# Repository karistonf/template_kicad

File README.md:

# Template Kicad

Some templates that are very useful for developing PCBs in KiCad

The components in the template include:

* A symmetrical power supply with an input of 5 volts and outputs of +12 volts and -12 volts.
* Can (Controller Area Network) module
* A buck power supply with an input of 12 volts and an output of 3.3 volts.
* A microcontroller, the STM32F103, featuring a High-speed external (HSE) crystal, a Low-speed external (LSE) crystal for the RTC, a 3.3V battery backup for the RTC, power indicator LEDs, a USB connector, and a programming connector with a JST jack.

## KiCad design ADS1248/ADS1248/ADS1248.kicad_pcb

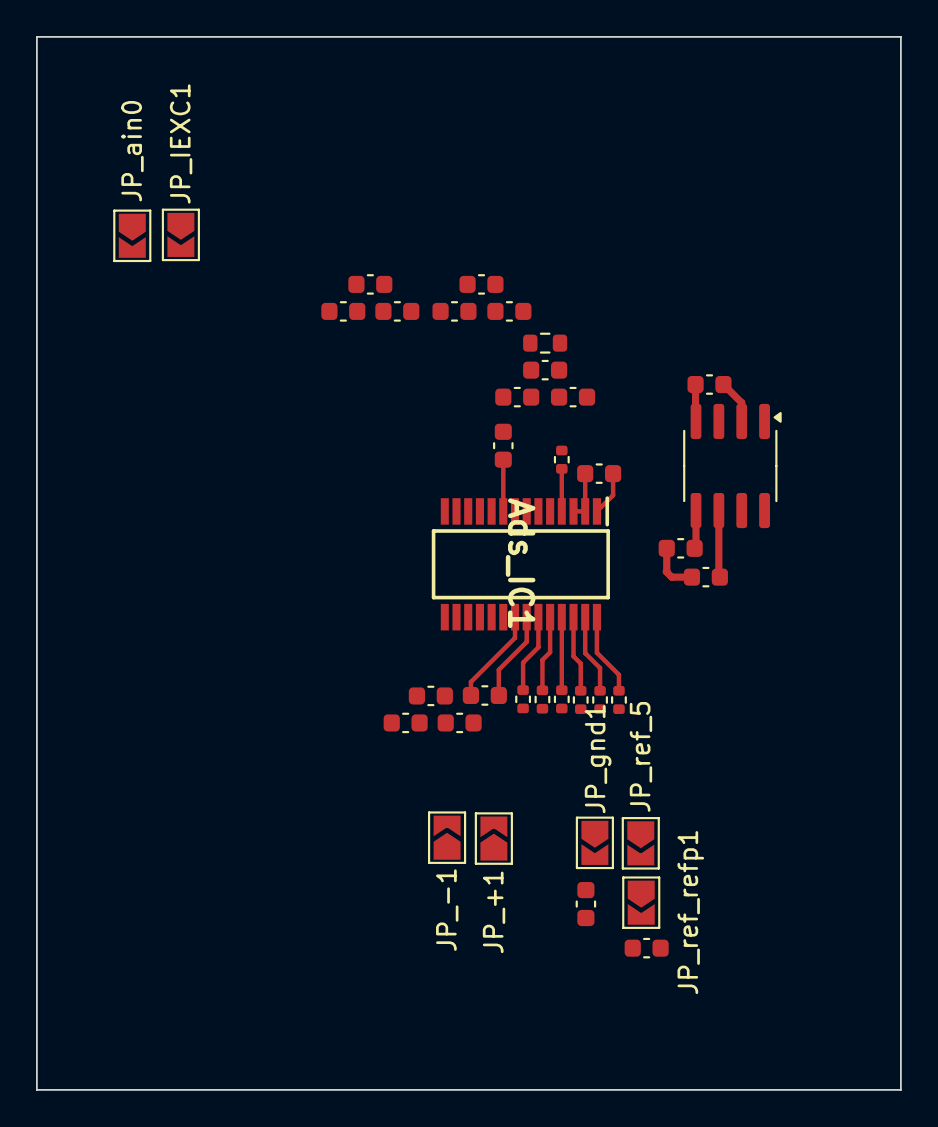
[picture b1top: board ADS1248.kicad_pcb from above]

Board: 2 copper layers, 48.0 x 58.5 mm, 37 parts (0 on the bottom side), 22 nets.

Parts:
Ads_C1, Ads_C2, Ads_C3: 0.1uF; C_0603_1608Metric
Ads_IC1: ADS1248IPWR; SOP65P640X120-28N
Ads_R1, Ads_R2, Ads_R3, Ads_R4, Ads_R5, Ads_R6, Ads_R7: 47; R_0402_1005Metric
Ads_ain_C1, Ads_ain_C2, Ads_ain_C3, Ads_ain_C4, Ads_ain_C5, Ads_ain_C6: 0.1uF; C_0603_1608Metric
Ads_ref_0_C1, Ads_ref_0_C2, Ads_ref_0_C3, Ads_ref_1_C1, Ads_ref_1_C2: 0.1uF; C_0603_1608Metric
CRTD_I_CM5, CRTD_I_CM6: C; C_0603_1608Metric
CRTD_I_DIFF3: C; C_0603_1608Metric
JP_+1: Jumper_2_Open; SolderJumper-2_P1.3mm_Open_TrianglePad1.0x1.5mm
JP_-1: Jumper_2_Open; SolderJumper-2_P1.3mm_Open_TrianglePad1.0x1.5mm
JP_IEXC1: Jumper_2_Open; SolderJumper-2_P1.3mm_Open_TrianglePad1.0x1.5mm
JP_ain0: Jumper_2_Open; SolderJumper-2_P1.3mm_Open_TrianglePad1.0x1.5mm
JP_gnd1: Jumper_2_Open; SolderJumper-2_P1.3mm_Open_TrianglePad1.0x1.5mm
JP_ref_5: Jumper_2_Open; SolderJumper-2_P1.3mm_Open_TrianglePad1.0x1.5mm
JP_ref_refp1: Jumper_2_Open; SolderJumper-2_P1.3mm_Open_TrianglePad1.0x1.5mm
REF1: 10K; R_0603_1608Metric
Ref_C1, Ref_C3: 1uF; C_0603_1608Metric
Ref_C2: 22uF; C_0603_1608Metric
U1: REF5050AD; SOIC-8_3.9x4.9mm_P1.27mm

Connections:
+3.3V: Ads_C1.1, Ads_IC1.1 (DVDD)
/5V: Ref_C1.2, U1.2 (Vin)
AVDD: Ads_C3.1, Ads_IC1.22 (AVDD), JP_ref_5.2 (B), JP_ref_refp1.1 (A), Ref_C2.1, U1.6 (Vout)
AVSS: Ads_C1.2, Ads_C2.2, Ads_C3.2, Ads_IC1.2 (DGND), Ads_IC1.3 (CLK), Ads_IC1.8 (REFN1), Ads_IC1.10 (VREFCOM), Ads_IC1.21 (AVSS), Ads_ain_C1.1, Ads_ain_C3.2, Ads_ain_C4.1, Ads_ain_C6.2, Ads_ref_0_C1.1, Ads_ref_0_C3.2, Ads_ref_1_C1.1, Ads_ref_1_C2.2, CRTD_I_CM5.1, CRTD_I_CM6.2, JP_gnd1.2 (B), Ref_C1.1, Ref_C2.2, Ref_C3.2, U1.4 (GND)
IEXC1: Ads_IC1.20 (IEXC1), JP_IEXC1.1 (A)
unnamed: Ads_IC1.27 (DIN), Ads_R3.1
unnamed: Ads_IC1.26 (DOUT/~DRDY), Ads_R4.1
unnamed: Ads_IC1.28 (SCLK), Ads_R2.1
unnamed: Ads_IC1.23 (START), Ads_R7.1
unnamed: Ads_IC1.24 (~CS), Ads_R6.1
unnamed: Ads_IC1.25 (~DRDY), Ads_R5.1
unnamed: Ads_IC1.4 (~RESET), Ads_R1.2
unnamed: Ref_C3.1, U1.5 (Trim/NR)
REFN0: Ads_IC1.6 (REFN0/GPIO1), Ads_ref_0_C2.2, Ads_ref_0_C3.1, REF1.1
REFP0: Ads_IC1.5 (REFP0/GPIO0), Ads_IC1.14 (AIN5/IEXC/GPIO5), Ads_IC1.17 (AIN2/IEXC/GPIO2), Ads_ain_C2.2, Ads_ain_C3.1, Ads_ain_C5.2, Ads_ain_C6.1, Ads_ref_0_C1.2, Ads_ref_0_C2.1, REF1.2
REFP1: Ads_IC1.7 (REFP1), Ads_ref_1_C1.2, Ads_ref_1_C2.1, JP_ref_refp1.2 (B)
VRefOut: Ads_C2.1, Ads_IC1.9 (VREFOUT)
ain0: Ads_IC1.11 (AIN0/IEXC), JP_ain0.1 (A)
ain1: Ads_IC1.12 (AIN1/IEXC), Ads_ain_C4.2, Ads_ain_C5.1, JP_IEXC1.2 (B), JP_ain0.2 (B)
ain3: Ads_IC1.13 (AIN4/IEXC/GPIO4), Ads_IC1.18 (AIN3/IEXC/GPIO3), Ads_ain_C1.2, Ads_ain_C2.1
ain6: Ads_IC1.15 (AIN6/IEXC/GPIO6), CRTD_I_CM5.2, CRTD_I_DIFF3.1, JP_+1.2 (B)
ain7: Ads_IC1.16 (AIN7/IEXC/GPIO7), CRTD_I_CM6.1, CRTD_I_DIFF3.2, JP_-1.2 (B)

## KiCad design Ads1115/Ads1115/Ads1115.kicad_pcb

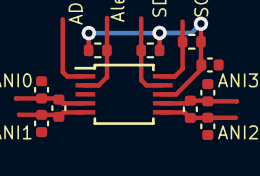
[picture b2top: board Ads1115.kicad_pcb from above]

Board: 2 copper layers, 11 parts (0 on the bottom side), 9 nets.

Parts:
ADC_Alert_R1: 10k; R_0402_1005Metric
ADC_C1, ADC_C2, ADC_C3, ADC_C4, ADC_C5, ADC_C6, ADC_C7: 0.1uF; C_0402_1005Metric
ADC_SCL_R1: 10k; R_0402_1005Metric
ADC_SDA_R1: 10k; R_0402_1005Metric
ADS1115_U1: ADS1115IDGS; TSSOP-10_3x3mm_P0.5mm

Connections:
+5V: ADC_Alert_R1.1, ADC_C1.2, ADC_SCL_R1.1, ADC_SDA_R1.2, ADS1115_U1.8 (VDD)
/Alert: ADC_Alert_R1.2, ADS1115_U1.2 (ALERT/RDY)
/SCL: ADC_SCL_R1.2, ADS1115_U1.10 (SCL)
/SDA: ADC_SDA_R1.1, ADS1115_U1.9 (SDA)
A0: ADC_C2.2, ADC_C6.2, ADS1115_U1.4 (AIN0)
A1: ADC_C3.2, ADC_C6.1, ADS1115_U1.5 (AIN1)
A2: ADC_C4.2, ADC_C7.1, ADS1115_U1.6 (AIN2)
A3: ADC_C5.2, ADC_C7.2, ADS1115_U1.7 (AIN3)
GND: ADC_C1.1, ADC_C2.1, ADC_C3.1, ADC_C4.1, ADC_C5.1, ADS1115_U1.1 (ADDR), ADS1115_U1.3 (GND)

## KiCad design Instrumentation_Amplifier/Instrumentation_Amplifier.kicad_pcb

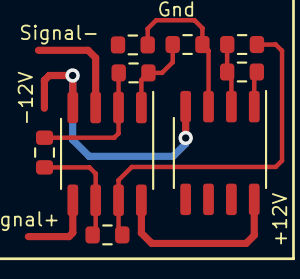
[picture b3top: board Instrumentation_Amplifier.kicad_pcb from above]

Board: 2 copper layers, 9 parts (0 on the bottom side), 9 nets.

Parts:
IA_R1: 1k; R_0603_1608Metric
IA_R2, IA_R3: 470; R_0603_1608Metric
IA_R4, IA_R5: 10k; R_0603_1608Metric
IA_R6, IA_R7: 100k; R_0603_1608Metric
IA_U1, IA_U2: LM358; SO-8_3.9x4.9mm_P1.27mm

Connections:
+12L: IA_U1.8 (V+), IA_U2.8 (V+)
-12V: IA_U1.4 (V-), IA_U2.4 (V-)
/Signal_Out: IA_R7.1, IA_U2.1
unnamed: IA_R2.2, IA_R5.1, IA_U1.1
unnamed: IA_R3.2, IA_R4.1, IA_U1.7
unnamed: IA_R1.2, IA_R2.1, IA_U1.2 (-)
unnamed: IA_R1.1, IA_R3.1, IA_U1.6 (-)
unnamed: IA_R5.2, IA_R6.2, IA_U2.3 (+)
unnamed: IA_R4.2, IA_R7.2, IA_U2.2 (-)

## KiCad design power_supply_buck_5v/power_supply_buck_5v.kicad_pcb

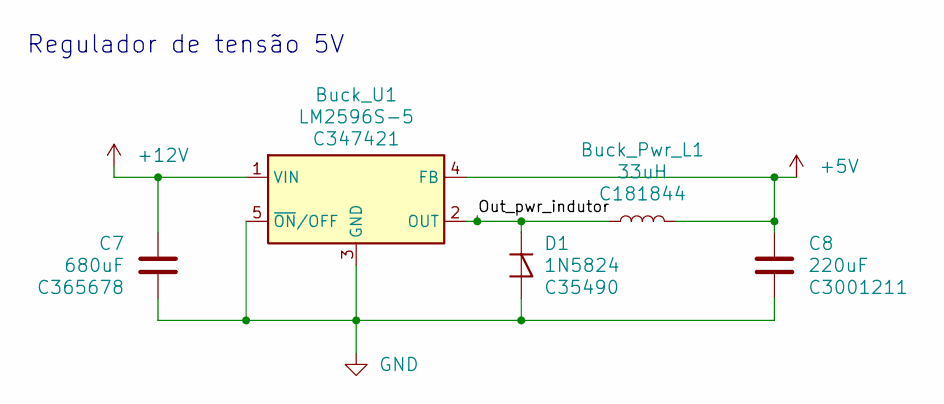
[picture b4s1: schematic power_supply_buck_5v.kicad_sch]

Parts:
Buck_Pwr_L1: 33uH; L_12x12mm_H8mm; LCSC C181844
Buck_U1: LM2596S-5; TO-263-5_TabPin3; LCSC C347421
C7: 680uF; CP_Elec_10x10.5; LCSC C365678
C8: 220uF; CP_Elec_6.3x5.4; LCSC C3001211
D1: 1N5824; D_SMB; LCSC C35490

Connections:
+5V: Buck_Pwr_L1.2, Buck_U1.4 (FB), C8.1
+12V: Buck_U1.1 (VIN), C7.1
/Out_pwr_indutor: Buck_Pwr_L1.1, Buck_U1.2 (OUT), D1.1 (K)
GND: Buck_U1.3 (GND), Buck_U1.5 (~ON/OFF), C7.2, C8.2, D1.2 (A)

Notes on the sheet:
Regulador de tensão 5V

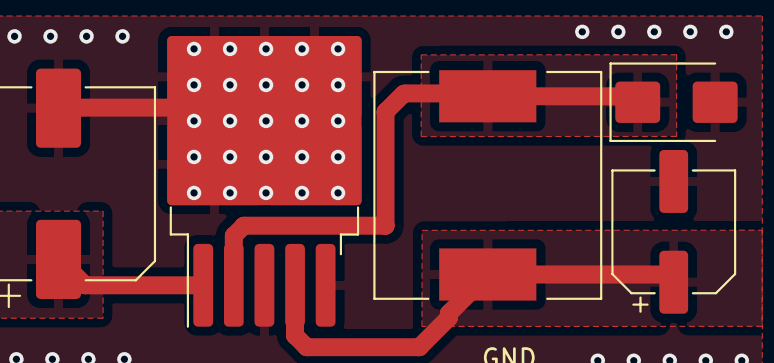
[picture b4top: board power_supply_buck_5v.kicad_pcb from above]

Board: 2 copper layers, 5 parts (0 on the bottom side), 4 nets.

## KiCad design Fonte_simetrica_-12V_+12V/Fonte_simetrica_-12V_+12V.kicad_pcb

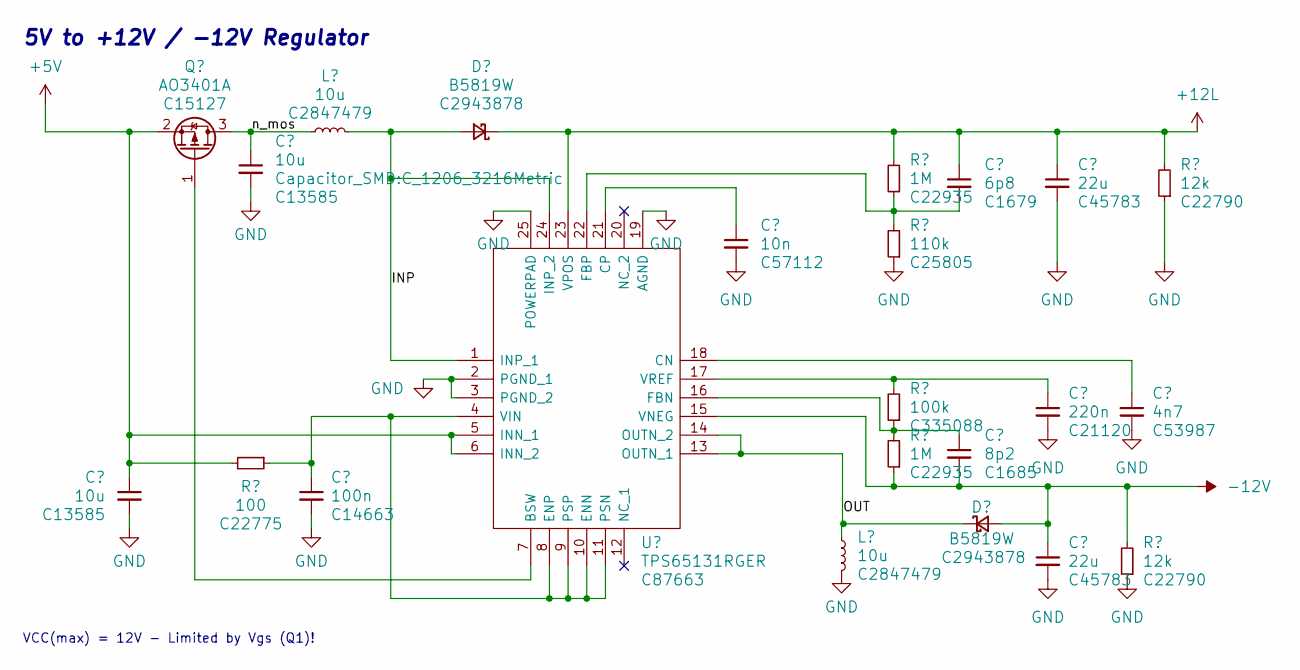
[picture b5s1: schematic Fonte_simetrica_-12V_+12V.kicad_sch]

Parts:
CFS1, CFS2: 10u; C_1206_3216Metric; LCSC C13585
CFS3: 100n; C_0603_1608Metric; LCSC C14663
CFS4: 10n; C_0603_1608Metric; LCSC C57112
CFS5: 6p8; C_0603_1608Metric; LCSC C1679
CFS6: 8p2; C_0603_1608Metric; LCSC C1685
CFS7: 220n; C_0603_1608Metric; LCSC C21120
CFS8, CFS9: 22u; C_0805_2012Metric; LCSC C45783
CFS10: 4n7; C_0603_1608Metric; LCSC C53987
DFS1, DFS2: B5819W; D_SOD-123; LCSC C2943878
LFS1, LFS2: 10u; L_TracoPower_TCK-047_5.2x5.8mm; LCSC C2847479
QFS1: AO3401A; SOT-23; LCSC C15127
RFS1: 100; R_0603_1608Metric; LCSC C22775
RFS2, RFS5: 1M; R_0603_1608Metric; LCSC C22935
RFS3: 110k; R_0603_1608Metric; LCSC C25805
RFS4: 100k; R_0603_1608Metric; LCSC C335088
RFS6, RFS7: 12k; R_0603_1608Metric; LCSC C22790
UFS1: TPS65131RGER; QFN-24-1EP_4x4mm_P0.5mm_EP2.6x2.6mm; Mouser2 Part Number 595-TPS65131RGET

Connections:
+5V: CFS1.1, QFS1.2 (S), RFS1.2, UFS1.5 (INN_1), UFS1.6 (INN_2)
+12L: CFS5.1, CFS9.1, DFS1.1 (K), RFS2.2, RFS7.2, UFS1.23 (VPOS)
-12V: CFS6.2, CFS8.1, DFS2.2 (A), RFS5.1, RFS6.2, UFS1.15 (VNEG)
/INP: DFS1.2 (A), LFS1.2, UFS1.1 (INP_1), UFS1.24 (INP_2)
/OUT: DFS2.1 (K), LFS2.1, UFS1.13 (OUTN_1), UFS1.14 (OUTN_2)
/n_mos: CFS2.1, LFS1.1, QFS1.3 (D)
GND: CFS1.2, CFS2.2, CFS3.2, CFS4.2, CFS7.2, CFS8.2, CFS9.2, CFS10.2, LFS2.2, RFS3.1, RFS6.1, RFS7.1, UFS1.2 (PGND_1), UFS1.3 (PGND_2), UFS1.19 (AGND), UFS1.25 (POWERPAD)
unnamed: QFS1.1 (G), UFS1.7 (BSW)
unnamed: CFS10.1, UFS1.18 (CN)
unnamed: CFS4.1, UFS1.21 (CP)
unnamed: CFS3.1, RFS1.1, UFS1.4 (VIN), UFS1.8 (ENP), UFS1.9 (PSP), UFS1.10 (ENN), UFS1.11 (PSN)
unnamed: CFS6.1, RFS4.1, RFS5.2, UFS1.16 (FBN)
unnamed: CFS5.2, RFS2.1, RFS3.2, UFS1.22 (FBP)
unnamed: CFS7.1, RFS4.2, UFS1.17 (VREF)

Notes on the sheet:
5V to +12V / -12V Regulator
VCC(max) = 12V - Limited by Vgs (Q1)!

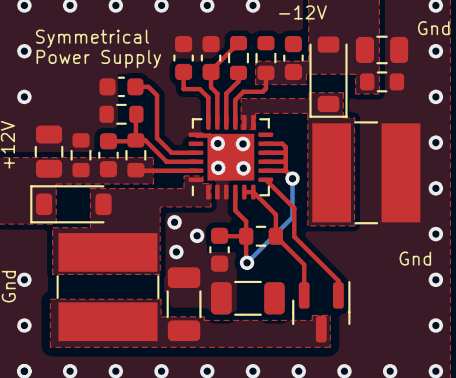
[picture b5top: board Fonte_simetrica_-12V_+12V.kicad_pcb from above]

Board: 2 copper layers, 23 parts (0 on the bottom side), 14 nets.

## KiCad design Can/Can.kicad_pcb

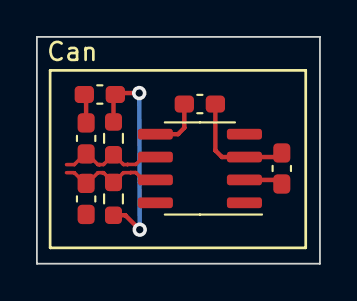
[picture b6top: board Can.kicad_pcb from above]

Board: 2 copper layers, 15.7 x 12.6 mm, 8 parts (0 on the bottom side), 6 nets.

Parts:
Can_C1, Can_C2: 100pF; C_0603_1608Metric_Pad1.08x0.95mm_HandSolder
Can_C3: 4,7uF; C_0603_1608Metric_Pad1.08x0.95mm_HandSolder
Can_R1, Can_R2: 60; R_0603_1608Metric_Pad0.98x0.95mm_HandSolder
Can_in_C1: 47nF; C_0603_1608Metric_Pad1.08x0.95mm_HandSolder
Can_in_C2: 100nF; C_0603_1608Metric_Pad1.08x0.95mm_HandSolder
TJA1: TJA1051T-3; SOIC-8_3.9x4.9mm_P1.27mm

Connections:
+3V3: Can_in_C2.1, TJA1.5 (VIO)
+5V: Can_in_C1.1, Can_in_C2.2, TJA1.3 (VCC)
/Can+: Can_C1.2, Can_R2.1, TJA1.7 (CANH)
/Can-: Can_C2.2, Can_R1.1, TJA1.6 (CANL)
GND: Can_C1.1, Can_C2.1, Can_C3.1, Can_in_C1.2, TJA1.2 (GND)
unnamed: Can_C3.2, Can_R1.2, Can_R2.2

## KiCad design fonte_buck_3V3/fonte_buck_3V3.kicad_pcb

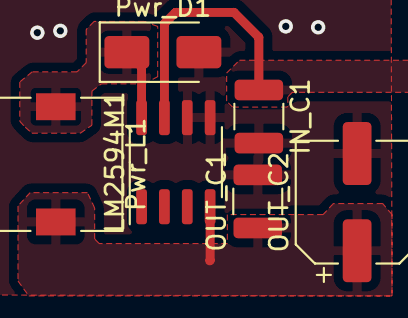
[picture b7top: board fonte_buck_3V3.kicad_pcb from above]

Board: 2 copper layers, 6 parts (0 on the bottom side), 4 nets.

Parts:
IN_C1: 10uF; C_1210_3225Metric
LM2594M1: LM2594M-3.3; SOIC-8_3.9x4.9mm_P1.27mm
OUT_C1: 100uF; C_1210_3225Metric
OUT_C2: C; CP_Elec_6.3x7.7
Pwr_D1: D; D_SMA
Pwr_L1: 100uH; L_7.3x7.3_H4.5

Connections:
+3V3: LM2594M1.4 (FB), OUT_C1.1, OUT_C2.1, Pwr_L1.2
+12V: IN_C1.1, LM2594M1.7 (VIN)
/Net_diodo: LM2594M1.8 (OUT), Pwr_D1.1 (K), Pwr_L1.1
GND: IN_C1.2, LM2594M1.5 (~ON/OFF), LM2594M1.6 (GND), OUT_C1.2, OUT_C2.2, Pwr_D1.2 (A)

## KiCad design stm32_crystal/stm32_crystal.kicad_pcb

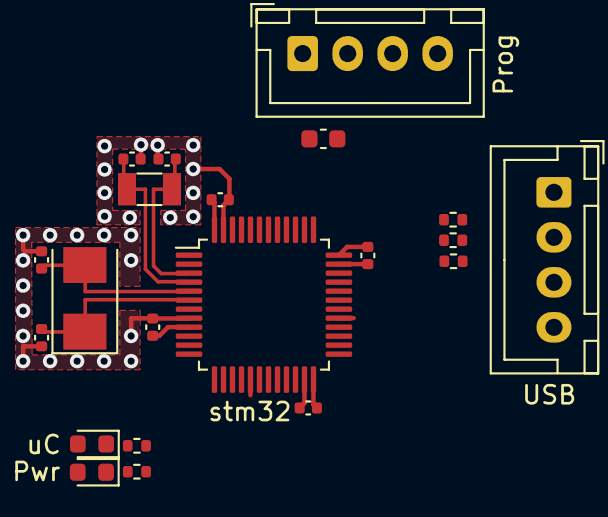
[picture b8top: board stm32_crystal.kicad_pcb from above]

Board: 2 copper layers, 21 parts (0 on the bottom side), 16 nets.

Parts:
CC1, CC2: 33pF; C_0402_1005Metric
LED_R1, LED_R2: 510; R_0402_1005Metric
PWR_LED1: LED; LED_0603_1608Metric
Prog1: Conn_01x04_Female; JST_XH_B4B-XH-A_1x04_P2.50mm_Vertical
Prog_C1: 104; C_0603_1608Metric
RTC_C1, RTC_C2: 22pF; C_0402_1005Metric
RTC_Y1: Crystal_Small; Crystal_SMD_3215-2Pin_3.2x1.5mm
U1: STM32F103C6Tx; LQFP-48_7x7mm_P0.5mm
USB1: Conn_01x04_Female; JST_XH_B4B-XH-A_1x04_P2.50mm_Vertical
USB_R1, USB_R2: 20; R_0402_1005Metric
USB_R3: 4.7k; R_0402_1005Metric
Vdd1, Vdd2, Vdd3, Vdd4: 100nF; C_0402_1005Metric
uC_LED1: LED; LED_0603_1608Metric
uC_Y1: 8Mhz; Crystal_SMD_5032-2Pin_5.0x3.2mm

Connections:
+3V3: PWR_LED1.2 (A), Prog1.1, Prog_C1.1, U1.9 (VDDA), U1.24 (VDD), U1.36 (VDD), U1.48 (VDD), Vdd1.1, Vdd2.1, Vdd3.1, Vdd4.1
/D+: U1.33 (PA12), USB_R1.1, USB_R3.1
/D-: U1.32 (PA11), USB_R2.1
/OSC+: CC2.1, U1.6 (PD1), uC_Y1.1
/OSC-: CC1.2, U1.5 (PD0), uC_Y1.2
/OSC_RTC+: RTC_C1.1, RTC_Y1.1, U1.4 (PC15)
/OSC_RTC-: RTC_C2.1, RTC_Y1.2, U1.3 (PC14)
/usb+: USB1.2, USB_R1.2
/usb-: USB1.3, USB_R2.2
GND: CC1.1, CC2.2, LED_R1.2, LED_R2.2, Prog1.4, Prog_C1.2, RTC_C1.2, RTC_C2.2, U1.8 (VSSA), U1.23 (VSS), U1.35 (VSS), U1.47 (VSS), USB1.4, Vdd1.2, Vdd2.2, Vdd3.2, Vdd4.2
Led_placa: U1.13 (PA3), uC_LED1.2 (A)
unnamed: LED_R2.1, PWR_LED1.1 (K)
unnamed: USB1.1, USB_R3.2
unnamed: LED_R1.1, uC_LED1.1 (K)
Swclk: Prog1.2, U1.37 (PA14)
Swdio: Prog1.3, U1.34 (PA13)

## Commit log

2023-11-10 add power supply buck 5v
2023-11-22 update stm32 cristal
2023-12-13 changes in stm and add can module
2023-12-14 changes power_supply_buck_5v add layout
2023-12-14 readme
2023-12-15 fix layout stm32
2024-02-05 add power 12+ and 12-
2024-02-27 add ads1111 and ads1248
2024-02-28 sinc
2024-03-01 updates ads1115 and ads 1248
2024-03-07 add ads1248, RTD multiple sensors 2 wires
